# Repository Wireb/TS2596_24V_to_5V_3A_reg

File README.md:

# TS2596 24V to 5V@3A regulator
This design is a simple breakout card for the TS2596 buck 40V Vin to 5V @ 3A Vout regulator. 
Main reason was to supply a 5V USB socket for a web cam off the 24V supply in my Prusa 3d printer. 

License is MIT so do what you want with it just don't litigate me. 

## KiCad
This is a KiCad 5.1.0 project. 

Gerber data and spreadsheet of the bill of materials can be found in here. 

## OSHpark PCBs
V0 PCB design can be found here:
https://oshpark.com/shared_projects/jKUSeUO9

V1 just added polarity marks to the back silk screen (Square pad is positive) 

## Build notes
I just used a iron to assemble most of the cards starting with the smallest component and worked my way up. 
The regulator thermal pad was a pain. None of my irons could get it hot enough. Ended up using a hot air gun to heat the board and pad to solder them. 
If you have a reflow oven or skillet recomend using it for this part. Rest can be hand soldered with no issues. 

Copyright (c) 2019 Peter Shabino

Permission is hereby granted, free of charge, to any person obtaining a copy of this hardware, software, and associated documentation files 
(the "Product"), to deal in the Product without restriction, including without limitation the rights to use, copy, modify, merge, publish, 
distribute, sublicense, and/or sell copies of the Product, and to permit persons to whom the Product is furnished to do so, subject to the 
following conditions:

The above copyright notice and this permission notice shall be included in all copies or substantial portions of the Product.

THE PRODUCT IS PROVIDED "AS IS", WITHOUT WARRANTY OF ANY KIND, EXPRESS OR IMPLIED, INCLUDING BUT NOT LIMITED TO THE WARRANTIES OF 
MERCHANTABILITY, FITNESS FOR A PARTICULAR PURPOSE AND NONINFRINGEMENT. IN NO EVENT SHALL THE AUTHORS OR COPYRIGHT HOLDERS BE LIABLE 
FOR ANY CLAIM, DAMAGES OR OTHER LIABILITY, WHETHER IN AN ACTION OF CONTRACT, TORT OR OTHERWISE, ARISING FROM, OUT OF OR IN CONNECTION 
WITH THE PRODUCT OR THE USE OR OTHER DEALINGS IN THE PRODUCT.

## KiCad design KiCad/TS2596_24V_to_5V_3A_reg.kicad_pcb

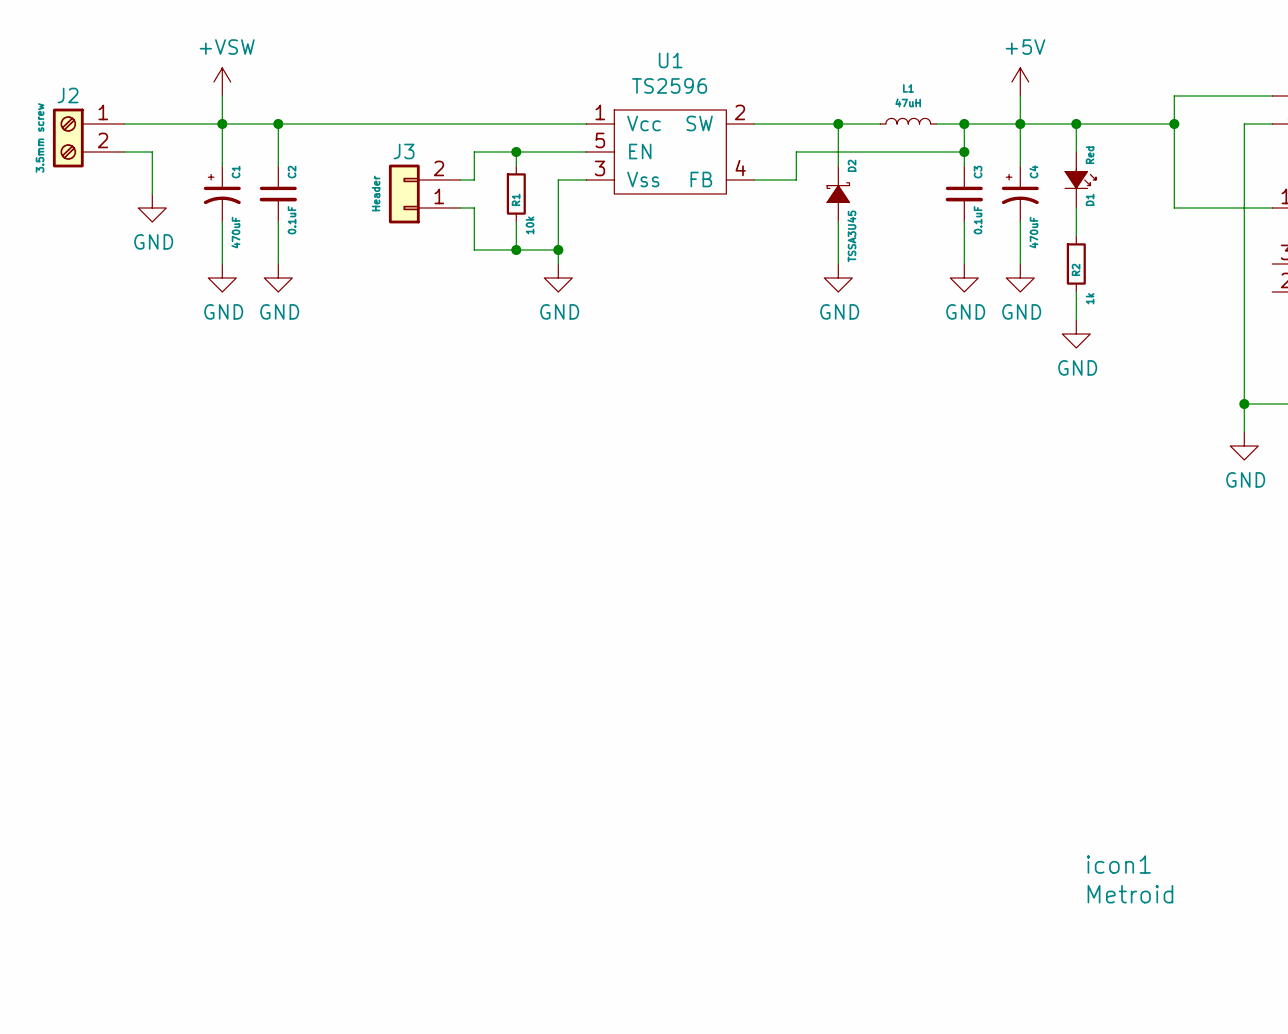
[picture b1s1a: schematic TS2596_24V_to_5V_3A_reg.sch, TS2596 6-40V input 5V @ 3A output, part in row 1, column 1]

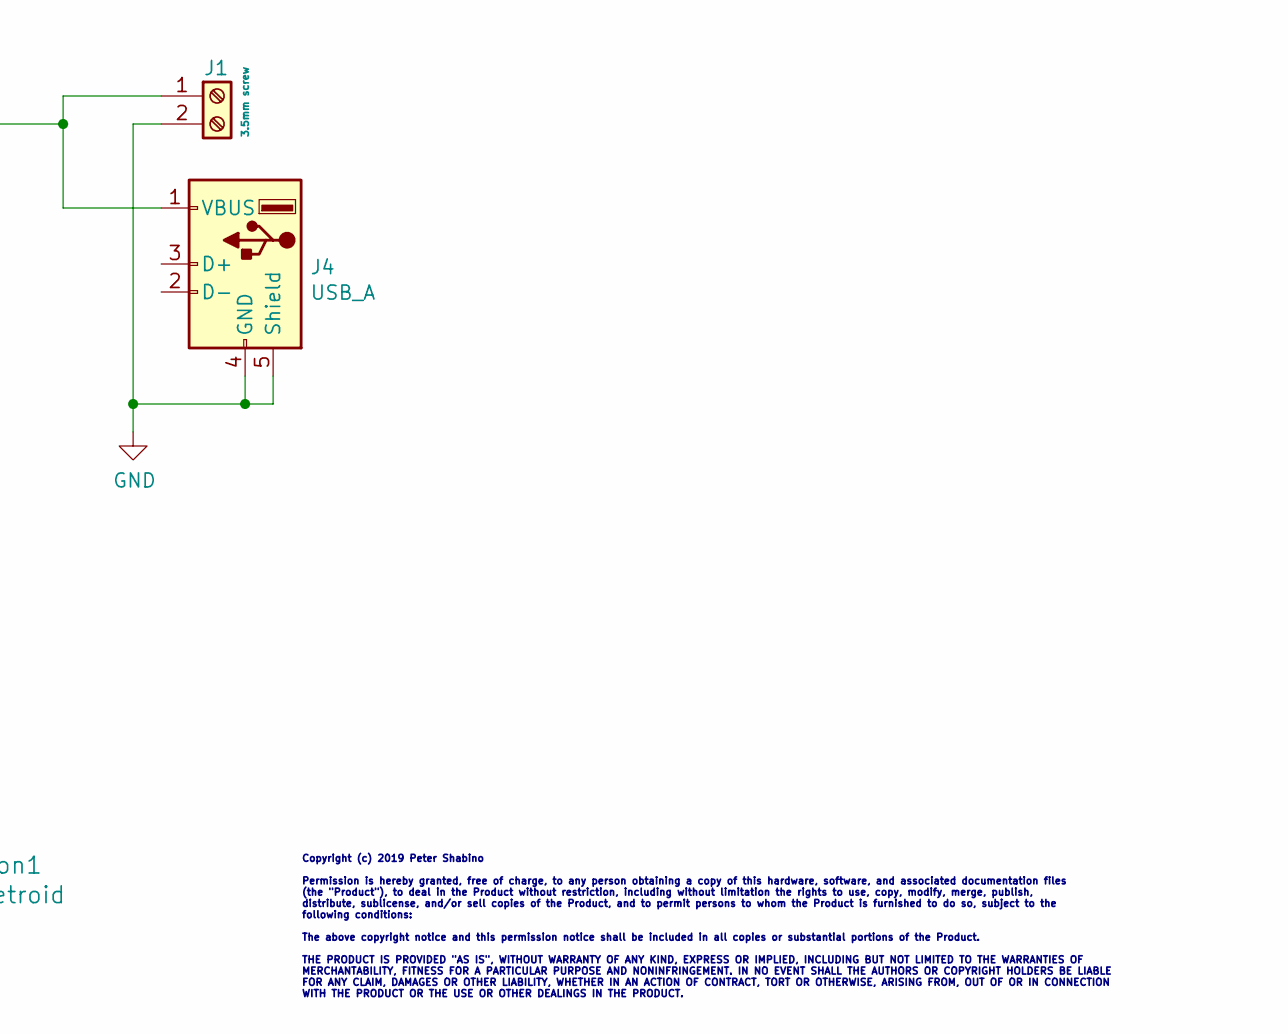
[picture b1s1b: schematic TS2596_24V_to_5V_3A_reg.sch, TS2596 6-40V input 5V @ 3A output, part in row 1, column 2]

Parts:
C1: 470uF; EEE-FK1HxxxAM
C2, C3: 0.1uF; C_0805
C4: 470uF; EEE-HA1AxxxUP
D1: Red; LED_0805
D2: TSSA3U45; DO-214AC
J1, J2: 3.5mm screw; TerminalBlock_Phoenix_PT-3.5mm_2pol
J3: Header; Pin_Header_Straight_1x02_Pitch2.54mm
J4: USB_A
L1: 47uH; SRP1265A
R1: 10k; R_0805
R2: 1k; R_0805
U1: TS2596; TO-263-5_TabPin3
icon1: Metroid; metroid

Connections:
+5V: C3.1, C4.1, D1.2 (A), J1.1, J4.1 (VBUS), L1.2, U1.4 (FB)
+VSW: C1.1, C2.1, J2.1, U1.1 (Vcc)
GND: C1.2, C2.2, C3.2, C4.2, D2.2 (A), J1.2, J2.2, J3.1, J4.4 (GND), J4.5 (Shield), R1.2, R2.2, U1.3 (Vss)
unnamed: D1.1 (K), R2.1
unnamed: D2.1 (K), L1.1, U1.2 (SW)
unnamed: J3.2, R1.1, U1.5 (EN)

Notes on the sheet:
Copyright (c) 2019 Peter Shabino Permission is hereby granted, free of charge, to any person obtaining a copy of this hardware, software, and associated documentation files (the "Product"), to deal in the Product without restriction, including without limitation the rights to use, copy, modify, mer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

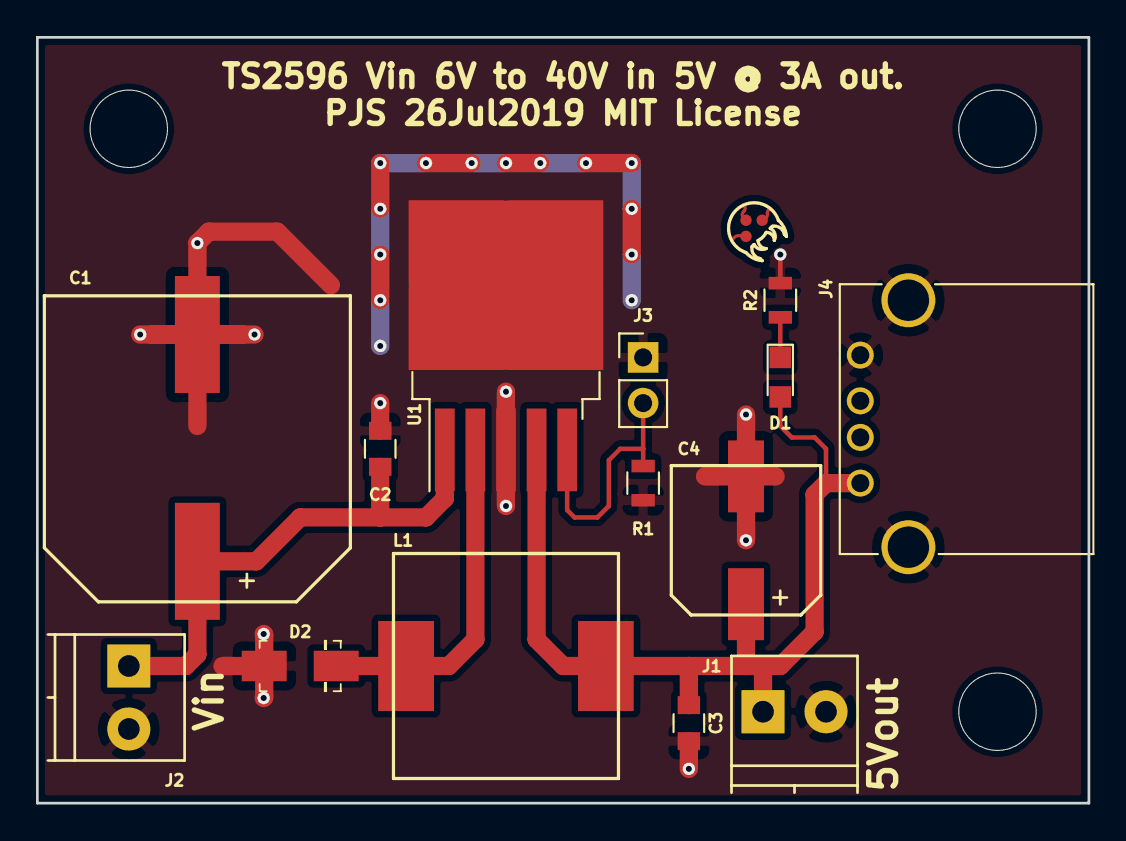
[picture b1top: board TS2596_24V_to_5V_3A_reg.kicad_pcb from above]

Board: 2 copper layers, 58.4 x 42.5 mm, 15 parts (0 on the bottom side), 6 nets.

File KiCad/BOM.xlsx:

Q | part number | footprint | ref_des | Have | mfg | mfg PN | Digikey Link
2 | 0.1uF | Capacitors_SMD:C_0805 | C2 C3 | y | Samsung | CL21F104ZBCNNNC | https://www.digikey.com/product-detail/en/samsung-electro-me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
1 | 10k | Resistors_SMD:R_0805 | R1 | y | Stackpole | RNCP0805FTD10K0 | https://www.digikey.com/product-detail/en/stackpole-electron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
1 | 1k | Resistors_SMD:R_0805 | R2 | y | Stackpole | RNCP0805FTD1K00 | https://www.digikey.com/product-detail/en/stackpole-electron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
2 | 3.5mm screw | TerminalBlocks_Phoenix:TerminalBlock_Phoenix_PT-3.5mm_2pol | J2 J1 | y | Phoenix | 1984617 | https://www.digikey.com/product-detail/en/phoenix-contact/19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
1 | 470uF | PJS_smt_parts:EEE-FK1HxxxAM | C1 | n | Panasonic | EEE-FK1H471AM | https://www.digikey.com/product-detail/en/panasonic-electron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
1 | 470uF | PJS_smt_parts:EEE-HA1AxxxUP | C4 | n | Panasonic | EEE-HA1A471UP | https://www.digikey.com/product-detail/en/panasonic-electron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
1 | 47uH | Bourns:SRP1265A | L1 | n | Bourns | SRP1265A-470M | https://www.digikey.com/product-detail/en/bourns-inc/SRP1265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
0 | Header | Pin_Headers:Pin_Header_Straight_1x02_Pitch2.54mm | J3
1 | Red | LEDs:LED_0805 | D1 | n | Wurth | 150080RS75000 | https://www.digikey.com/product-detail/en/wurth-electronics-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
1 | TS2596 | TO_SOT_Packages_SMD:TO-263-5_TabPin3 | U1 | n | Taiwan Semi | TS2596CM550 RNG | https://www.digikey.com/product-detail/en/taiwan-semiconduct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
1 | TSSA3U45 | digikey-footprints:DO-214AC | D2 | n | Taiwan Semi | TSSA3U45 R3G | https://www.digikey.com/product-detail/en/taiwan-semiconduct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
1 | USB_A | Connectors:USB_A | J4 | n | Stewart | SS-52100-001 | https://www.digikey.com/product-detail/en/stewart-connector/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

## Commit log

2019-08-11 First post

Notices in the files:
KiCad/TS2596_24V_to_5V_3A_reg.kicad_pcb:
PJS 26Jul2019 MIT License
